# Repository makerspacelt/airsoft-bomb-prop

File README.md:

This is the source code of an Airsoft prop [KMS-ANT](http://armory.makerspace.lt) designed and sold by [Kaunas Makerspace](https://makerspace.lt).

This repository contains:

* [sw/](/sw) - ESPHome-based C++ software licensed under [GPL-3.0](/sw/LICENSE)
* [hw/](/hw) - PCB designed using KiCad and licensed under [CERN-OHL-S](/hw/LICENSE)

You can buy the product here: https://www.tindie.com/products/makerspacelt/airsoft-bomb-prop-kms-ant/

More information: http://armory.makerspace.lt/

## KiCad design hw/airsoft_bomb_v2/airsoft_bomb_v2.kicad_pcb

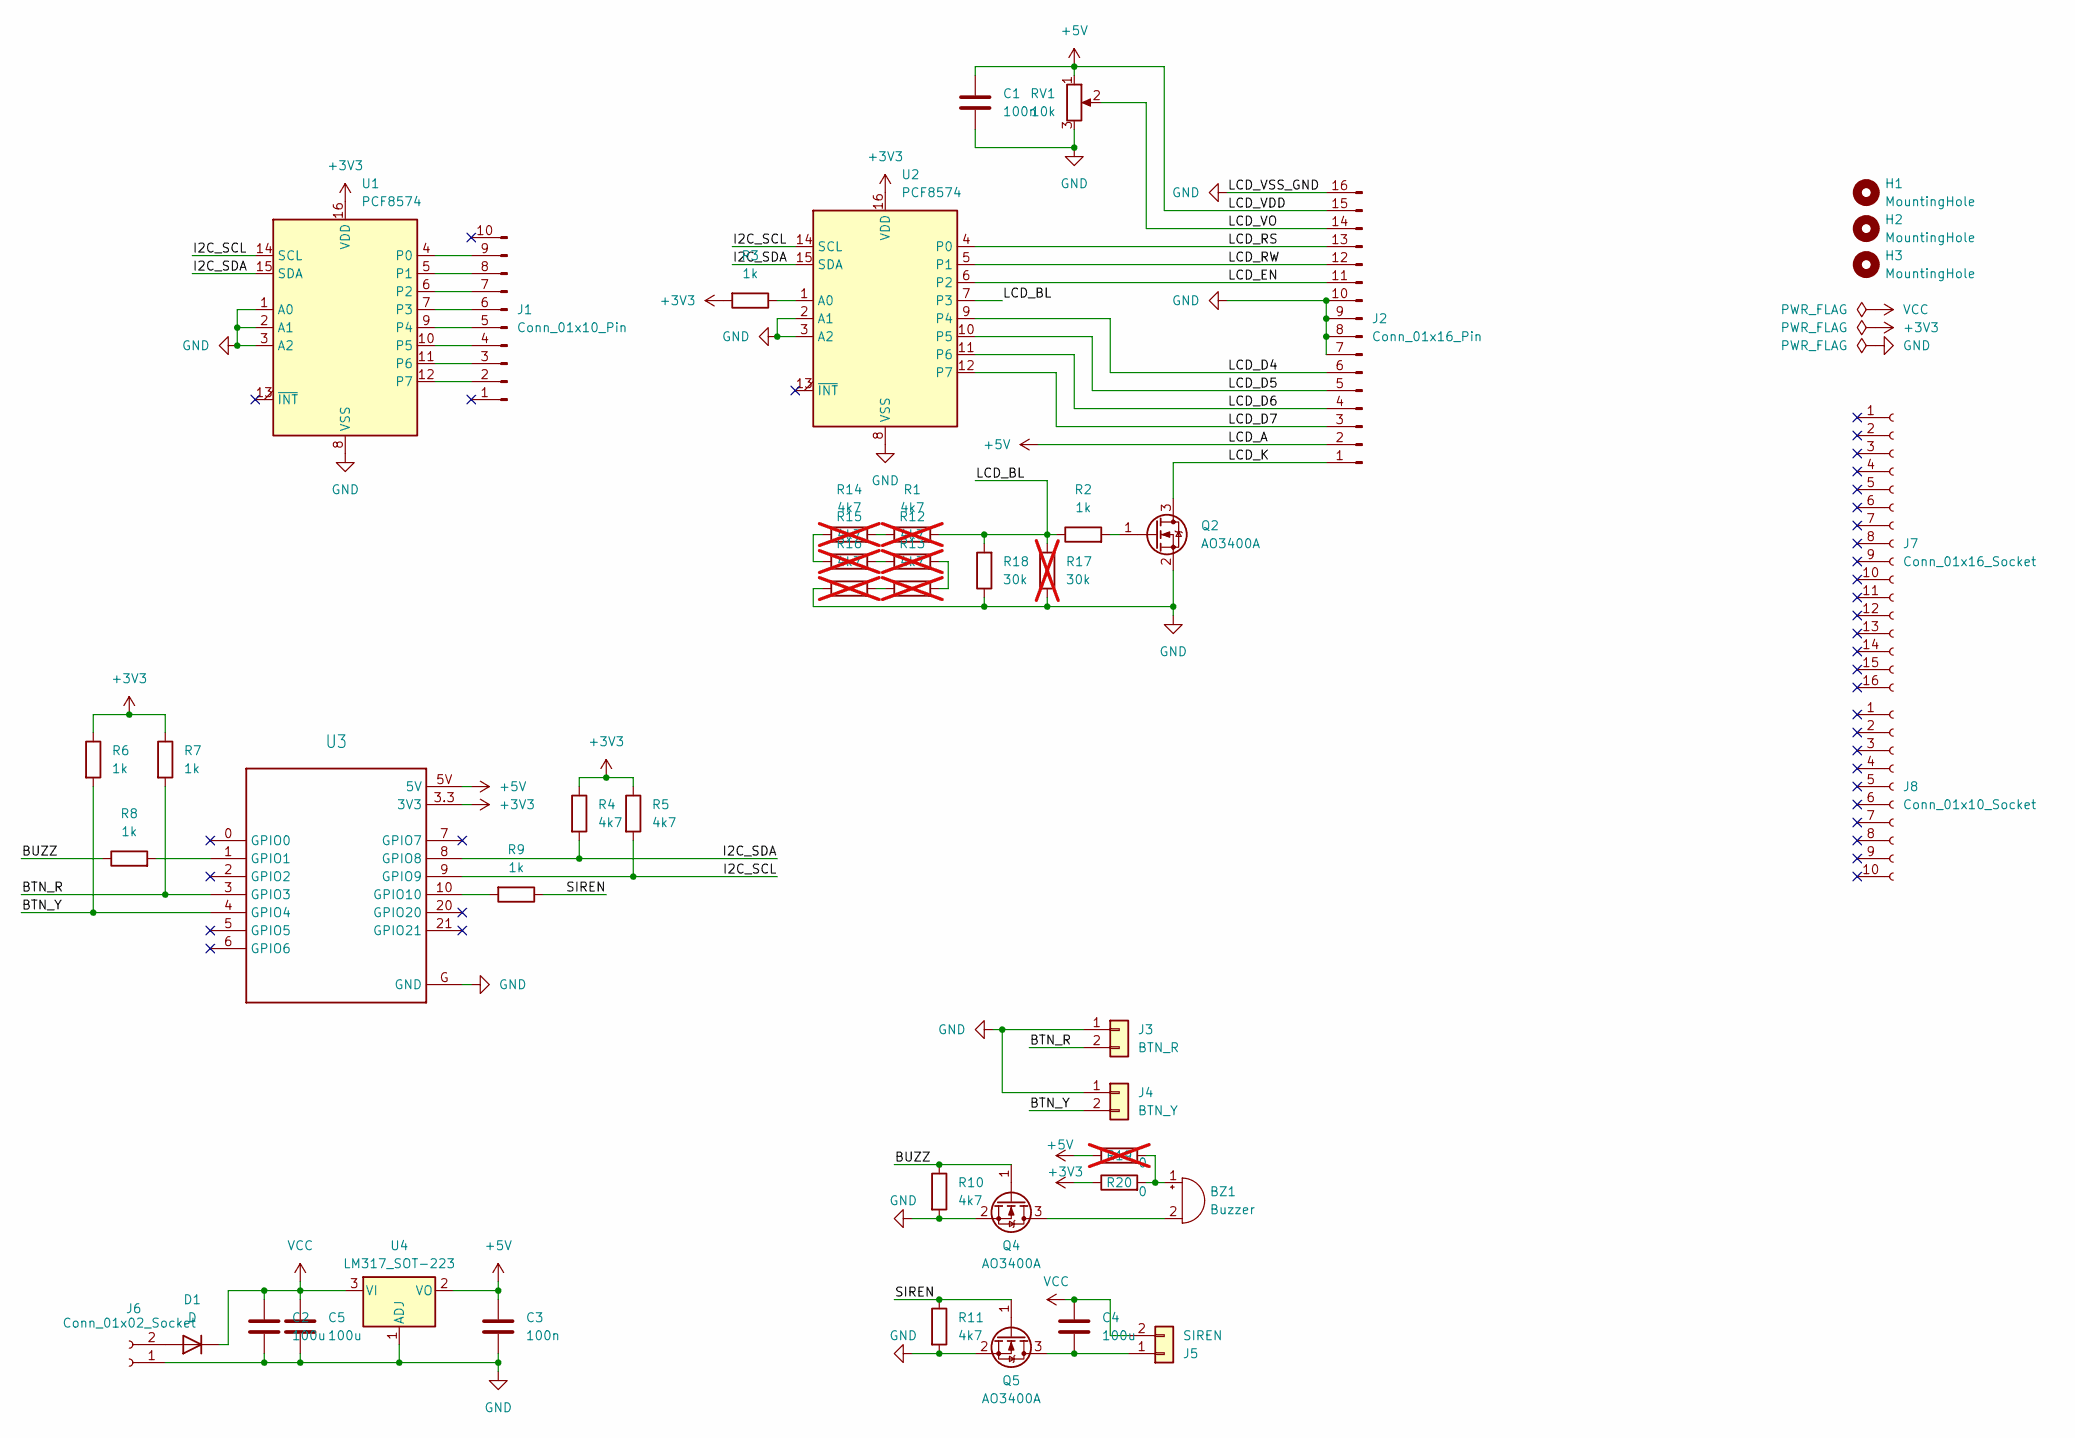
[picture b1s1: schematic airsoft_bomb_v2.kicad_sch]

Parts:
BZ1: Buzzer; Buzzer_12x9.5RM7.6
C1, C3: 100n; C_0805_2012Metric_Pad1.18x1.45mm_HandSolder; MPN C49678
C2, C4, C5: 100u; C_1206_3216Metric_Pad1.33x1.80mm_HandSolder; MPN C7432784
D1: D; D_SOD-123; MPN C8598
H1, H2, H3: MountingHole; MountingHole_3.2mm_M3
J1: Conn_01x10_Pin; keypad
J2: Conn_01x16_Pin; screen
J3: BTN_R; HIWA 250-21-2G
J4: BTN_Y; HIWA 250-21-2G
J5: SIREN; HIWA 250-21-2G
J6: Conn_01x02_Socket; PhoenixContact_MC_1,5_2-G-3.5_1x02_P3.50mm_Horizontal_with_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
J7: Conn_01x16_Socket; PinHeader_1x16_P2.54mm_Horizontal
J8: Conn_01x10_Socket; PinHeader_1x10_P2.54mm_Horizontal
Q2, Q4, Q5: AO3400A; SOT-23; MPN C8545
R1, R12, R13, R14, R15, R16: 4k7; R_0805_2012Metric_Pad1.20x1.40mm_HandSolder; MPN C17673; not fitted
R2, R3, R6, R7, R8, R9: 1k; R_0805_2012Metric_Pad1.20x1.40mm_HandSolder; MPN C17513
R4, R5, R10, R11: 4k7; R_0805_2012Metric_Pad1.20x1.40mm_HandSolder; MPN C17673
R17: 30k; R_Axial_DIN0207_L6.3mm_D2.5mm_P7.62mm_Horizontal; not fitted
R18: 30k; R_0805_2012Metric_Pad1.20x1.40mm_HandSolder; MPN C17621
R19: 0; R_0805_2012Metric_Pad1.20x1.40mm_HandSolder; MPN C17477; not fitted
R20: 0; R_0805_2012Metric_Pad1.20x1.40mm_HandSolder; MPN C17477
RV1: 10k; Potentiometer_Bourns_TC33X_Vertical; MPN C719176
U1, U2: PCF8574; SOIC-16W_7.5x10.3mm_P1.27mm; MPN C7605
U3: MODULE_ESP32-C3_SUPERMINI
U4: LM317_SOT-223; SOT-223-3_TabPin2; MPN C6187

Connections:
+3V3: R3.2, R4.1, R5.1, R6.1, R7.1, R20.1, U1.16 (VDD), U2.16 (VDD), U3.3.3 (3V3)
+5V: C1.1, C3.1, J2.2, J2.15, R19.1, RV1.1, U3.5V, U4.2 (VO)
/BTN_R: J3.2, R7.2, U3.3 (GPIO3)
/BTN_Y: J4.2, R6.2, U3.4 (GPIO4)
/BUZZ: Q4.1 (G), R8.1, R10.1
/I2C_SCL: R5.2, U1.14 (SCL), U2.14 (SCL), U3.9 (GPIO9)
/I2C_SDA: R4.2, U1.15 (SDA), U2.15 (SDA), U3.8 (GPIO8)
/LCD_BL: R1.2, R2.1, R17.2, R18.2, U2.7 (P3)
/LCD_D4: J2.6, U2.9 (P4)
/LCD_D5: J2.5, U2.10 (P5)
/LCD_D6: J2.4, U2.11 (P6)
/LCD_D7: J2.3, U2.12 (P7)
/LCD_EN: J2.11, U2.6 (P2)
/LCD_K: J2.1, Q2.3 (D)
/LCD_RS: J2.13, U2.4 (P0)
/LCD_RW: J2.12, U2.5 (P1)
/LCD_VO: J2.14, RV1.2
/SIREN: Q5.1 (G), R9.1, R11.1
GND: C1.2, C2.2, C3.2, C5.2, J2.7, J2.8, J2.9, J2.10, J2.16, J3.1, J4.1, J6.1, Q2.2 (S), Q4.2 (S), Q5.2 (S), R10.2, R11.2, R16.1, R17.1, R18.1, RV1.3, U1.1 (A0), U1.2 (A1), U1.3 (A2), U1.8 (VSS), U2.2 (A1), U2.3 (A2), U2.8 (VSS), U3.G (GND), U4.1 (ADJ)
unnamed: BZ1.1 (+), R19.2, R20.2
unnamed: BZ1.2 (-), Q4.3 (D)
unnamed: D1.2 (A), J6.2
unnamed: J1.2, U1.12 (P7)
unnamed: J1.3, U1.11 (P6)
unnamed: J1.4, U1.10 (P5)
unnamed: J1.5, U1.9 (P4)
unnamed: J1.6, U1.7 (P3)
unnamed: J1.7, U1.6 (P2)
unnamed: J1.8, U1.5 (P1)
unnamed: J1.9, U1.4 (P0)
unnamed: C4.2, J5.1, Q5.3 (D)
unnamed: Q2.1 (G), R2.2
unnamed: R1.1, R14.2
unnamed: R12.1, R15.2
unnamed: R12.2, R13.2
unnamed: R13.1, R16.2
unnamed: R14.1, R15.1
unnamed: R3.1, U2.1 (A0)
unnamed: R8.2, U3.1 (GPIO1)
unnamed: R9.2, U3.10 (GPIO10)
VCC: C2.1, C4.1, C5.1, D1.1 (K), J5.2, U4.3 (VI)

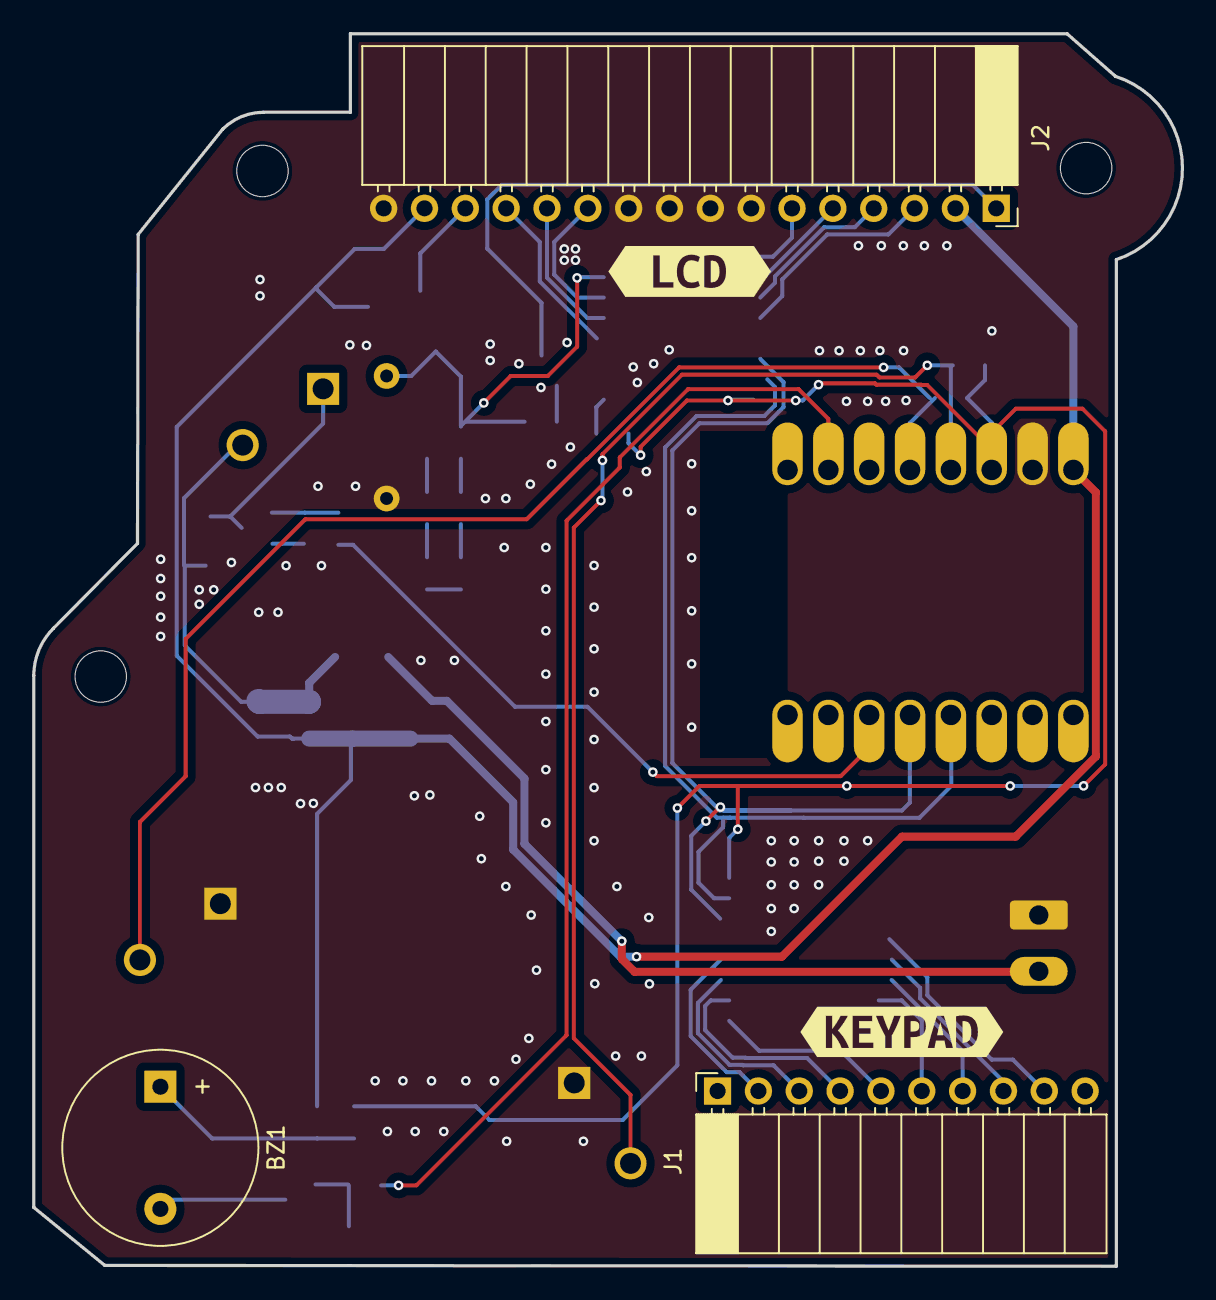
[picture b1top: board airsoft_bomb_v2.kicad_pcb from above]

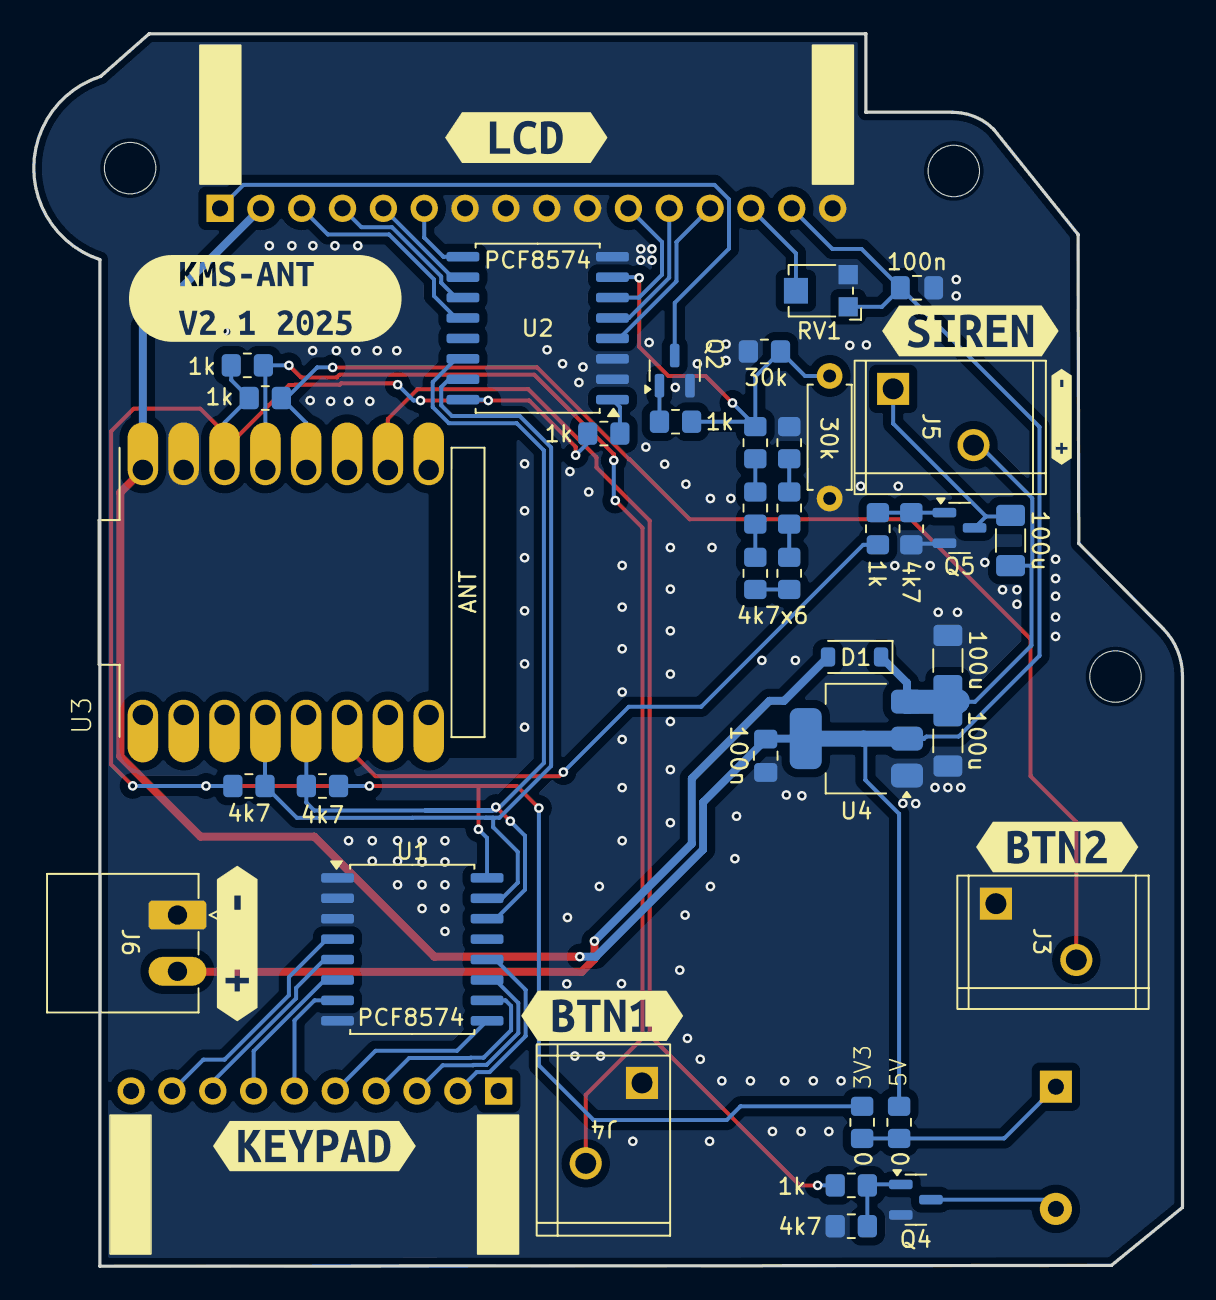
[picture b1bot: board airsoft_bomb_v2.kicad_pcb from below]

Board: 2 copper layers, 71.4 x 76.7 mm, 54 parts (49 on the bottom side), 41 nets.

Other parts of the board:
kibuzzard-67E6FC9B, kibuzzard-67E6FC9B#2: G***; kibuzzard-67E6FC9B
kibuzzard-67E6FC15: G***; kibuzzard-67E6FC15
kibuzzard-67E6FC26: G***; kibuzzard-67E6FC26
kibuzzard-67E6FC63, kibuzzard-67E6FC63#2: G***; kibuzzard-67E6FC63
kibuzzard-67E6FCB3: G***; kibuzzard-67E6FCB3
kibuzzard-67E6FE86: G***; kibuzzard-67E6FE86
kibuzzard-687FD9CC: G***; kibuzzard-687FD9CC
kibuzzard-68963AB1: G***; kibuzzard-68963AB1

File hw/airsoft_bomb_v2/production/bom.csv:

Designator,Footprint,Quantity,Value,LCSC Part #
BZ1,Buzzer_12x9.5RM7.6,1,Buzzer,
"C1, C3",0805,2,100n,C49678
"C2, C4, C5",1206,3,100u,C7432784
D1,D_SOD-123,1,D,C8598
J1,keypad,1,Conn_01x10_Pin,
J2,screen,1,Conn_01x16_Pin,
J3,HIWA 250-21-2G,1,BTN_R,
J4,HIWA 250-21-2G,1,BTN_Y,
J5,HIWA 250-21-2G,1,SIREN,
J6,"PhoenixContact_MC_1,5_2-G-3.5_1x02_P3.50mm_Horizontal_with_plug",1,Conn_01x02_Socket,
"Q2, Q4, Q5",SOT-23,3,AO3400A,C8545
"R10, R11, R4, R5",0805,4,4k7,C17673
R18,0805,1,30k,C17621
"R2, R3, R6, R7, R8, R9",0805,6,1k,C17513
R20,0805,1,0,C17477
RV1,Potentiometer_Bourns_TC33X_Vertical,1,10k,C719176
"U1, U2",SOIC-16W_7.5x10.3mm_P1.27mm,2,PCF8574,C7605
U3,MODULE_ESP32-C3_SUPERMINI,1,~,
U4,SOT-223-3_TabPin2,1,LM317_SOT-223,C6187

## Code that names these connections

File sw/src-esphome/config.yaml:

#
# Board
#

esp32:
  board: esp32-c3-devkitm-1
  framework:
    type: esp-idf

#
# esphome core
#

external_components:
  - source:
      type: local
      path: mycomponents

esphome:
  name: ant
  name_add_mac_suffix: true
  includes:
    - ../src-common
    - esphome-entry.hpp
  on_boot:
    - then:
        lambda: |-
          id(siren).turn_on();
          id(siren).set_level(0);
          id(buzzer).turn_on();
          id(buzzer).set_level(0);
          antg.action_set_siren_level(id(g_siren_level), false);
  on_shutdown:
    - then:
        lambda: |-
          id(siren).turn_off();
          id(buzzer).turn_off();

logger:
  level: DEBUG

preferences:
  flash_write_interval: 10s

mdns:
  disabled: true

#
# OTA config
#

wifi:
  id: mywifi
  enable_on_boot: false

  ap:
    password: 100decibel
    ap_timeout: 10s

ota:
  - platform: web_server
    on_begin:
      then:
        - lambda: |-
            id(my_display).print(0, 0, "    Updating    ");
            id(my_display).print(0, 1, "    firmware    ");
    on_error:
      then:
        - lambda: |-
            id(my_display).print(0, 0,  "    Updating    ");
            id(my_display).printf(0, 1, "   Error %d    ", x);

web_server:
  port: 80
  index_html_include: ./index.html

#
# Prop hardware
#

globals:
  - id: g_siren_level # 1-9
    type: int
    restore_value: true
    initial_value: "9"

output:
  - platform: ledc
    pin: GPIO1
    id: buzzer
    frequency: 1000Hz

  - platform: ledc
    pin: GPIO10
    id: siren

binary_sensor:
  # RED button
  - platform: gpio
    pin: GPIO3
    id: btn_r
    filters:
      - invert:
    on_press:
      lambda: |-
        ESP_LOGI("Key", "on_press RED");
        game_manager.handle_key(KEY_RED);
        id(my_display).update();
    on_release:
      lambda: |-
        ESP_LOGI("Key", "on_release RED");
        game_manager.handle_key(KEY_RED_RELEASE);
        id(my_display).update();

  # YELLOW button
  - platform: gpio
    pin: GPIO4
    id: btn_y
    filters:
      - invert:
    on_press:
      lambda: |-
        ESP_LOGI("Key", "on_press YELLOW");
        game_manager.handle_key(KEY_YELLOW);
        id(my_display).update();
    on_release:
      lambda: |-
        ESP_LOGI("Key", "on_release YELLOW");
        game_manager.handle_key(KEY_YELLOW_RELEASE);
        id(my_display).update();

  # C long press handling for game restart
  - platform: matrix_keypad
    keypad_id: mykeypad
    id: key_c
    key: C
    on_press:
      lambda: |-
        game_manager.key_c_press_at = millis();
    on_release:
      lambda: |-
        game_manager.key_c_press_at = 0;

  # D long press handling for organizer game reset
  - platform: matrix_keypad
    keypad_id: mykeypad
    id: key_d
    key: D
    on_press:
      lambda: |-
        game_manager.hard_reset_press_at = millis();
    on_release:
      lambda: |-
        game_manager.hard_reset_press_at = 0;

  # * long press handling for organizer game reset
  - platform: matrix_keypad
    keypad_id: mykeypad
    id: key_star
    key: "*"
    on_press:
      lambda: |-
        game_manager.hard_reset_press_at = millis();
    on_release:
      lambda: |-
        game_manager.hard_reset_press_at = 0;

matrix_keypad:
  id: mykeypad
  rows:
    - pin:
        pcf8574: pcf8574_hub
        number: 0
    - pin:
        pcf8574: pcf8574_hub
        number: 1
    - pin:
        pcf8574: pcf8574_hub
        number: 2
    - pin:
        pcf8574: pcf8574_hub
        number: 3
  columns:
    - pin:
        pcf8574: pcf8574_hub
        number: 4
    - pin:
        pcf8574: pcf8574_hub
        number: 5
    - pin:
        pcf8574: pcf8574_hub
        number: 6
    - pin:
        pcf8574: pcf8574_hub
        number: 7
  keys: "D#0*C987B654A321"
  has_diodes: false
  on_key:
    - lambda: |-
        ESP_LOGI("Key", "on_key %c", x);
        game_manager.handle_key(x);
        id(my_display).update();

i2c:
  - id: bus_a
    sda: GPIO8
    scl: GPIO9
    frequency: 300kHz

pcf8574:
  - id: "pcf8574_hub"
    address: 0x20
    pcf8575: false

display:
  - platform: lcd_pcf8574
    id: my_display
    i2c_id: bus_a
    dimensions: 16x2
    address: 0x21
    # update_interval: never
    user_characters:
      # right arrow
      - position: 0
        data:
          - 0b11000
          - 0b01100
          - 0b00110
          - 0b11111
          - 0b11111
          - 0b00110
          - 0b01100
          - 0b11000
      # progress bars
      - position: 1
        data:
          - 0b10000
          - 0b10000
          - 0b10000
          - 0b10000
          - 0b10000
          - 0b10000
          - 0b10000
          - 0b10000
      - position: 2
        data:
          - 0b11000
          - 0b11000
          - 0b11000
          - 0b11000
          - 0b11000
          - 0b11000
          - 0b11000
          - 0b11000
      - position: 3
        data:
          - 0b11100
          - 0b11100
          - 0b11100
          - 0b11100
          - 0b11100
          - 0b11100
          - 0b11100
          - 0b11100
      - position: 4
        data:
          - 0b11110
          - 0b11110
          - 0b11110
          - 0b11110
          - 0b11110
          - 0b11110
          - 0b11110
          - 0b11110
      - position: 5
        data:
          - 0b11111
          - 0b11111
          - 0b11111
          - 0b11111
          - 0b11111
          - 0b11111
          - 0b11111
          - 0b11111
    lambda: |-
      game_manager.display_update(it);

script:
  - id: s_start_buzzer
    parameters:
      duration: int
      level: float
      tone: int
    mode: single
    then:
      - output.ledc.set_frequency:
          id: buzzer
          frequency: !lambda return tone;
      - output.set_level:
          id: buzzer
          level: !lambda return level;
      - delay: !lambda return duration;
      - output.set_level:
          id: buzzer
          level: 0

  - id: s_start_siren
    parameters:
      delay: int
      duration: int
      level: float
      tone: int
    mode: restart
    then:
      - delay: !lambda return delay;
      - output.ledc.set_frequency:
          id: siren
          frequency: !lambda return tone;
      - output.set_level:
          id: siren
          level: !lambda return level;
      - delay: !lambda return duration;
      - output.set_level:
          id: siren
          level: 0

  - id: s_stop_siren
    then:
      - output.set_level:
          id: siren
          level: 0

  - id: s_start_ota
    then:
      lambda: |-
        id(mywifi).enable();
        antg.ota_info.ssid = wifi::global_wifi_component->get_ap().get_ssid();
        antg.ota_info.psk = wifi::global_wifi_component->get_ap().get_password();
        antg.ota_info.ip = wifi::global_wifi_component->wifi_soft_ap_ip().str();

  - id: s_stop_ota
    then:
      lambda: |-
        id(mywifi).disable();

  - id: s_handle_actions
    then:
      lambda: |-
        uint32_t actions = antg.actions;
        if (actions > 0) {
          if (actions & ACTION_SAVE_SIREN_LEVEL) {
            id(g_siren_level) = antg.settings.siren_level_user;
          }
          if (actions & ACTION_START_SIREN) {
            ant_siren_t *s = &antg.siren_params;
            id(s_start_siren)->execute(s->delay, s->duration, s->level, s->tone);
          }
          if (actions & ACTION_STOP_SIREN) {
            id(s_stop_siren)->execute();
          }
          if (actions & ACTION_START_BUZZER) {
            ant_buzzer_t *b = &antg.buzzer_params;
            id(s_start_buzzer)->execute(b->duration, b->level, b->tone);
          }
          if (actions & ACTION_START_OTA) {
            id(s_start_ota)->execute();
          }
          if (actions & ACTION_STOP_OTA) {
            id(s_stop_ota)->execute();
          }
        }

interval:
  - interval: 50ms
    then:
      - lambda: |-
          uint32_t now = millis();
          game_manager.clock(now, now - game_manager.clock_last_update_ms);
          id(my_display).update();

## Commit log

2025-06-27 setup
2025-07-04 pcb files
2025-07-14 Initial upload of the software codebase
2025-07-15 Added missing features to readme file
2025-07-15 Implement hard reset to main menu and fixed and fixed issue when after R/Y/* button press duration function was executed, the timer even though reset, but started counting again without needing anoth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
2025-07-15 Implement game reset after ending for all game modes
2025-07-15 Fixed duplicate entries in readme file
2025-07-15 Fixed the inputs so C is only for select and * will clear any input
2025-07-17 update SW TODOs
2025-07-17 update pcb step file
2025-07-18 add kibot.sh and required fixes
2025-07-21 fix wrong header model fix pcb interferes with screen screw
2025-07-22 mark creen/keypad connectors on other side of pcb mark siren +/-
2025-08-01 Move C++ code from esphome lambdas to separate files and implement PC build
    * Implemented a PC build with integration tests
    * Implemented remaining TODOs
2025-08-01 move siren pin to something that is not high on boot
2025-08-01 move siren to gpio10, fix defusal bad code timer
2025-08-05 Add Back menu to all modes. Fix D key in settings.
2025-08-05 zone control: add setup menu with start / back
2025-08-05 add splash screen
2025-08-05 do not beep on C_LONG press unless it does an action
2025-08-05 fix domination restart with C_LONG
2025-08-05 defusal: only beep while armed
2025-08-05 defusal/buttons: add missing break after case to fix states
2025-08-05 defusal code: fix bomb_ms_remaining type
2025-08-05 defusal more fixes & add tests
2025-08-05 defusal: add test where bad code is entered when 20s are remaining
2025-08-08 version silkscreen
2025-08-13 makefile: add a format target
2025-08-13 add OTA support
2025-08-13 fix menu tests after ota implementation
2025-08-13 fix defusal bomb timer - it should not tick before it's armed
2025-08-13 fix defusal game delay timer
2025-08-13 reorganize the sw project
2025-08-13 esphome config: simplify OTA progress display
2025-08-13 do not buzz for C long press if it does no action and buzz on press during splashscreen
2025-08-13 increase siren volume for medium setting
2025-08-13 makefile: print compiled firmware path
2025-08-13 stop siren on reset and on C_LONG press
2025-08-13 fix tests after siren changes
2025-08-13 split defusal & settings subhandlers into separate files
2025-08-13 do not override previous buzzer if it's already beeping
    (needed for respawn timer)
2025-08-13 respawn timer: rename respawn->standby, duration->respawn
2025-08-13 add test mode to settings
2025-08-13 defusal: fix countdown buzzer when armed
2025-08-13 modify siren volume, improve isren test & use low/med/high for siren level
2025-08-13 domination: add game end siren delay
2025-09-03 cleanup .pyc files added by mistake
2025-09-03 add png with qr code to the manual
2025-09-03 run clang format on all code
2025-09-03 update makefile
2025-09-03 update gitignore
2025-09-03 update makefile #2
2025-09-03 move esphome-entry.hpp to src-esphome/
2025-09-03 test.sh: print number of tests ran, exit with error on test fails
2025-09-03 update tests: buzzer beeps immediatelly after arming
2025-09-03 fix tests: adjust MEDIUM siren level
2025-09-03 esphome.sh: use docker or podman for building
2025-09-03 Add a test for test/eng mode
2025-09-03 tests: add tests for respawn timer mode
2025-09-03 Add CI.
2025-09-03 github workflow: add esphome fw build
2025-09-03 restrict the sw workflow to sw/ dir
2025-09-03 ci: save esphome firmware after build
2025-09-03 ci: also trigger sw workflow when it changes
2025-09-03 ci: adjust names
2025-09-03 ci: adjust names #2
2025-09-03 ci: split artifacts
2025-09-03 ci: cache esphome downloads
2025-09-03 ci: add cache key
2025-09-03 ci: add esphome fw build (#1)
2025-09-03 ci: fix caching & add manual trigger
2025-09-03 ci: fix caching & add manual trigger (#2)
2025-09-03 ci: run workflow when a tag is pushed
2025-09-03 makefile: add release target
2025-09-03 CI: implement release via CI (#3)
2025-09-03 makefile: update make release target
2025-09-05 change potentiometer to smd
2025-09-12 add polarity protection diode on voltage input lcsc part numbers
